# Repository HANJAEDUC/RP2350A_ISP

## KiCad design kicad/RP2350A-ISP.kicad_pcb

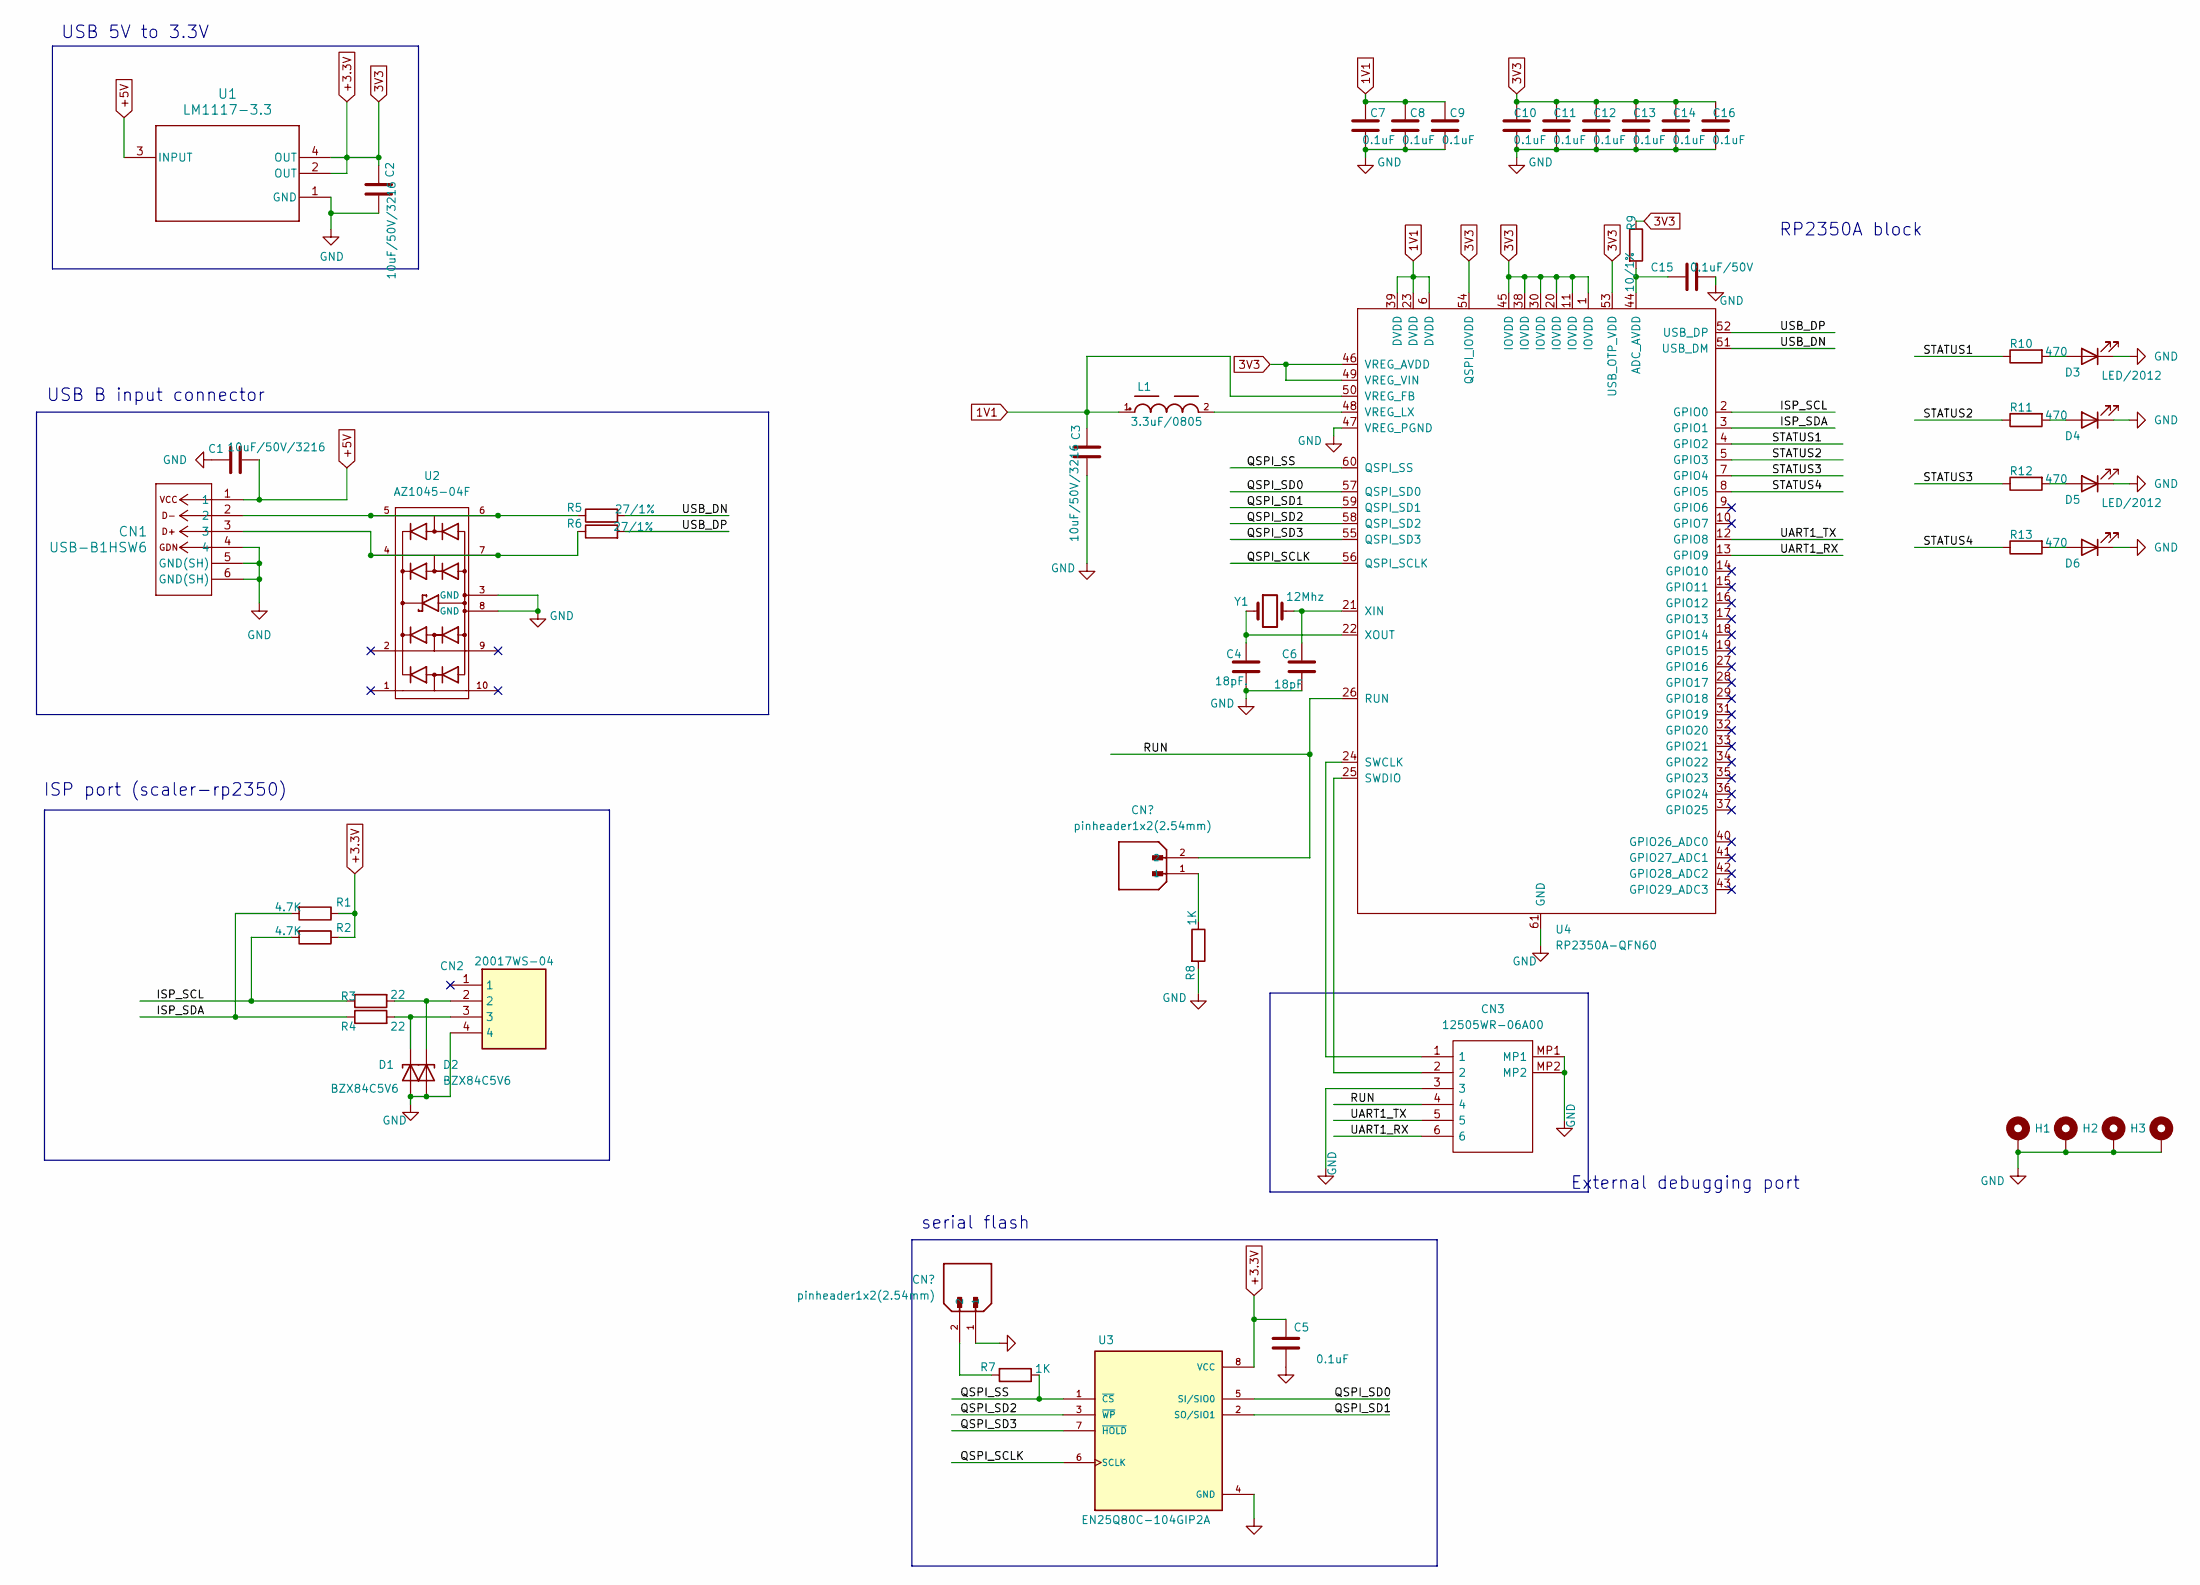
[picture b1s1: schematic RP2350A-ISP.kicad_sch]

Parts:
C1, C2, C3: 10uF/50V/3216; SMD-CAPACITOR(3216-1206)
C4: 18pF.; SMD-CAPACITOR(1608-0603)
C5, C7, C8, C9, C10, C11, C12, C13, C14, C16: 0.1uF; SMD-CAPACITOR(1608-0603)
C6: 18pF; SMD-CAPACITOR(1608-0603)
C15: 0.1uF/50V; SMD-CAPACITOR(1608-0603)
CN1: USB-B1HSW6; USB-B-CONN_USB-B1HSW6_OST
CN2: 20017WS-04
CN3: 12505WR-06A00; 12505WR06A00_1; Manufacturer_Part_Number 12505WR-06A00
D1, D2: BZX84C5V6
D3, D4, D5, D6: LED/2012; LED_0805_2012Metric
H1, H2, H3, H4: MountingHole_Pad; MountingHole_4mm_Pad_TopBottom
L1: 3.3uF/0805; SMD-RESISTOR(2012-0805)
R1, R2: 4.7K; SMD-RESISTOR(1608-0603)
R3, R4: 22; SMD-RESISTOR(1608-0603)
R5, R6: 27/1%; SMD-RESISTOR(1608-0603)
R7, R8: 1K; SMD-RESISTOR(1608-0603)
R9: 10/1%; SMD-RESISTOR(1608-0603)
R10, R11, R12, R13: 470; SMD-RESISTOR(1608-0603)
U1: LM1117-3.3; LM1117(SOT-223)
U2: AZ1045-04F; PARTREV N
U3: EN25Q80C-104GIP2A; MX25L8006EM1I-12G; PARTREV 1.6
U4: RP2350A-QFN60; RP2350A_QFN-60_EP_7.75x7.75_Pitch0.4mm
Y1: 12Mhz; Crystal_SMD_HC49-SD

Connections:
1V1: C3.1, C7.2, C8.2, C9.2, L1.1, U4.6 (DVDD), U4.23 (DVDD), U4.39 (DVDD), U4.50 (VREG_FB)
+3.3V: C2.1, C5.1, C10.2, C11.2, C12.2, C13.2, C14.2, C16.2, R1.1, R2.1, R9.1, U1.2 (OUT), U1.4 (OUT), U3.8 (VCC), U4.1 (IOVDD), U4.11 (IOVDD), U4.20 (IOVDD), U4.30 (IOVDD), U4.38 (IOVDD), U4.45 (IOVDD), U4.46 (VREG_AVDD), U4.49 (VREG_VIN), U4.53 (USB_OTP_VDD), U4.54 (QSPI_IOVDD)
+5V: C1.2, CN1.1, U1.3 (INPUT)
/ISP_SCL: R2.2, R3.1, U4.2 (GPIO0)
/ISP_SDA: R1.2, R4.1, U4.3 (GPIO1)
/QSPI_SCLK: U3.6 (SCLK), U4.56 (QSPI_SCLK)
/QSPI_SD0: U3.5 (SI/SIO0), U4.57 (QSPI_SD0)
/QSPI_SD1: U3.2 (SO/SIO1), U4.59 (QSPI_SD1)
/QSPI_SD2: U3.3 (~WP), U4.58 (QSPI_SD2)
/QSPI_SD3: U3.7 (~HOLD), U4.55 (QSPI_SD3)
/QSPI_SS: R7.1, U3.1 (~CS), U4.60 (QSPI_SS)
/RUN: CN3.4, U4.26 (RUN); also elsewhere on the board
/STATUS1: R10.1, U4.4 (GPIO2)
/STATUS2: R11.1, U4.5 (GPIO3)
/STATUS3: R12.1, U4.7 (GPIO4)
/STATUS4: R13.1, U4.8 (GPIO5)
/UART1_RX: CN3.6, U4.13 (GPIO9)
/UART1_TX: CN3.5, U4.12 (GPIO8)
/USB_DN: R5.2, U4.51 (USB_DM)
/USB_DP: R6.2, U4.52 (USB_DP)
GND: C1.1, C2.2, C3.2, C4.1, C5.2, C6.1, C7.1, C8.1, C9.1, C10.1, C11.1, C12.1, C13.1, C14.1, C15.2, C16.1, CN1.4, CN1.5 (GND(SH)), CN1.6 (GND(SH)), CN2.4, CN3.3, CN3.MP1, CN3.MP2, D1.1 (A), D2.1 (A), D3.1 (K), D4.1 (K), D5.1 (K), D6.1 (K), H1.1, H2.1, H3.1, H4.1, R8.2, U1.1 (GND), U2.3 (GND), U2.8 (GND), U3.4 (GND), U4.47 (VREG_PGND), U4.61 (GND); also elsewhere on the board
unnamed: CN1.2, R5.1, U2.5, U2.6
unnamed: CN1.3, R6.1, U2.4, U2.7
unnamed: CN2.3, D1.3 (K), R4.2
unnamed: CN2.2, D2.3 (K), R3.2
unnamed: D3.2 (A), R10.2
unnamed: D4.2 (A), R11.2
unnamed: D5.2 (A), R12.2
unnamed: D6.2 (A), R13.2
unnamed 29: R7.2; also elsewhere on the board
unnamed 30: R8.1; also elsewhere on the board
unnamed: C15.1, R9.2, U4.44 (ADC_AVDD)
unnamed: CN3.1, U4.24 (SWCLK)
unnamed: CN3.2, U4.25 (SWDIO)
unnamed: L1.2, U4.48 (VREG_LX)
unnamed: C6.2, U4.21 (XIN), Y1.2
unnamed: C4.2, U4.22 (XOUT), Y1.1

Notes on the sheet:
External debugging port
ISP port (scaler-rp2350)
serial flash
USB B input connector
RP2350A block
USB 5V to 3.3V

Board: 2 copper layers, 50 parts (0 on the bottom side), 37 nets, no tracks yet.

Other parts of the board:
SW1, SW2: Tactswitch

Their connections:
/RUN: SW2.3, SW2.4; also elsewhere on the board
GND: SW1.3, SW1.4; also elsewhere on the board
unnamed 29: SW1.1, SW1.2; also elsewhere on the board
unnamed 30: SW2.1, SW2.2; also elsewhere on the board
